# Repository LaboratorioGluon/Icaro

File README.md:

# Ícaro's Sensor Box

Desarrollo de uno de los equipos que van a ser lanzados en el proyecto Ícaro, un proyecto organizado y retransmitido por _@Araba_ST_ y _@Labgluon_ en Twitch.

> [!TIP]
> El proyecto **Ícaro** busca lanzar un globo estratosférico (hasta unos 20-30km de altura), subiendo varios equipos, entre ellos: Uno de radioafionados con APRS y Repetidor U/V, y nuestro equipo de sensores.

Nuestro objetivo es aprender a desarrollar equipos más complejos, a lo que sumamos la dificultad de ser el primer proyecto realizado en comunidad con la gente de _www.twitch.tv/labgluon_. Añadiendo la incertidumbre de gestionar equipos remotos y que no han trabajado nunca juntos..

---
Dentro de las misiones concretas está:
- Prueba de comunicaciones Wifi con ESP32-CAM (o equivalente) y ver máximo rango.
    - Mejorar antenas 2.4Ghz
    - Implementar código de lectura y envío de vídeo por wifi en el ESP32.
- Registro de datos de telemetría de la súbida, y comunicación de estos mediante LoRa.
    - Lectura de BMI160, BME280, 2x PT1000 y GPS.
    - Envío por LoRa e intentar conectarnos a TinyGS
- Creación de PCBs modulares para:
    - La lectura de sensores GPS/IMU/Temp/Barómetro/...
    - Regulación de voltajes.
    - Comunicaciones

**Otras ideas** que se han planteado:
- Añadir un control a la antena para que apunte siempre al globo.
- Añadir panel solar 
- Poner un ESP32 a la intemperie y ver cuando deja de funcionar.

## Enlaces rápidos

- [Diseño General](Docs/Design.md)
- Modulos:
    - [SupplyBoard](Modules/SupplyBoard/Doc/SupplyBoard.md)
    - [SensorBoard](Modules/SensorBoard/Doc/SensorBoard.md)
    - [CamBoard](Modules/CamBoard/Doc/CameraBoard.md)

## Estructura de carpetas

```
Icaro
├── Docs                    # Documentacion general
│   ├── NamingAndCoding.md  # Normas para nombrar ficheros/variables ...
│   └── Design.md           # Diseño a alto nivel
├── IcaroSW/                # Carpeta donde integramos el software final
│   └── ... 
├── Mechanical/             # Diseños 3D y mecánicos
│   └── ... 
└── Modules/                  
│   ├── <Module>             # Una carpeta por tarjeta
│       ├── Doc             # Documentación de la tarjeta
│       ├── PCB             # Diseño de la PCB
│       ├── Software        # Software si el módulo es uno completo
│       └── Library         # Librería SW para manejar la tarjeta.
|   └── ...
```

La idea es que por cada tarjeta que diseñemos tengamos una librería de software pensada para usar los componentes de esa tarjeta. Y que luego, en _IcaroSW_ se haga el software que se considera el principal.

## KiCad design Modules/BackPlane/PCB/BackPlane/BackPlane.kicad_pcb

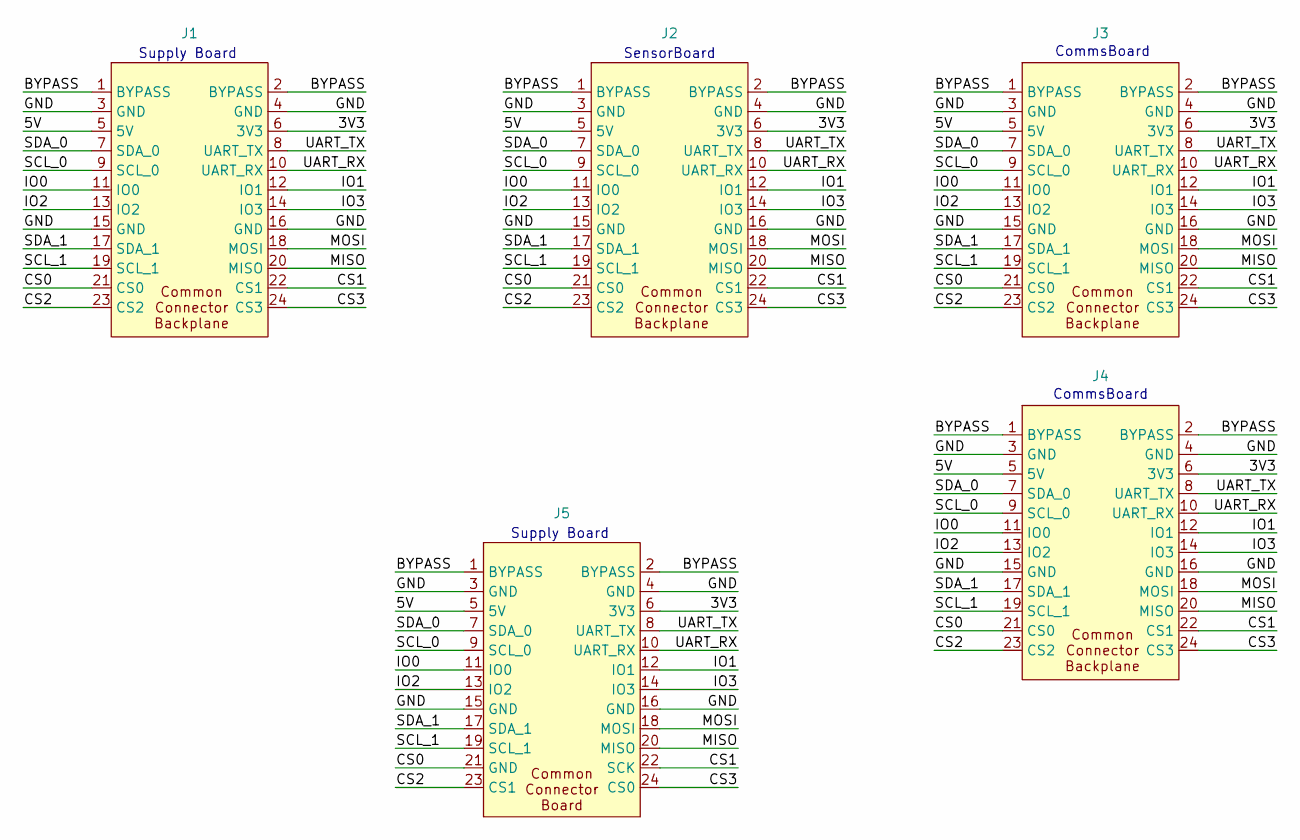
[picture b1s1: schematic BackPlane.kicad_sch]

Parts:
J1, J2, J3, J4: PinSocket_2x12_P2.54mm_Vertical
J5: Connector_Icaro_Edge_tarjeta

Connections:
/3V3: J1.6 (3V3), J2.6 (3V3), J3.6 (3V3), J4.6 (3V3), J5.6 (3V3)
/5V: J1.5 (5V), J2.5 (5V), J3.5 (5V), J4.5 (5V), J5.5 (5V)
/BYPASS: J1.1 (BYPASS), J1.2 (BYPASS), J2.1 (BYPASS), J2.2 (BYPASS), J3.1 (BYPASS), J3.2 (BYPASS), J4.1 (BYPASS), J4.2 (BYPASS), J5.1 (BYPASS), J5.2 (BYPASS)
/CS0: J1.21 (CS0), J2.21 (CS0), J3.21 (CS0), J4.21 (CS0), J5.21 (GND)
/CS1: J1.22 (CS1), J2.22 (CS1), J3.22 (CS1), J4.22 (CS1), J5.22 (SCK)
/CS2: J1.23 (CS2), J2.23 (CS2), J3.23 (CS2), J4.23 (CS2), J5.23 (CS1)
/CS3: J1.24 (CS3), J2.24 (CS3), J3.24 (CS3), J4.24 (CS3), J5.24 (CS0)
/IO0: J1.11 (IO0), J2.11 (IO0), J3.11 (IO0), J4.11 (IO0), J5.11 (IO0)
/IO1: J1.12 (IO1), J2.12 (IO1), J3.12 (IO1), J4.12 (IO1), J5.12 (IO1)
/IO2: J1.13 (IO2), J2.13 (IO2), J3.13 (IO2), J4.13 (IO2), J5.13 (IO2)
/IO3: J1.14 (IO3), J2.14 (IO3), J3.14 (IO3), J4.14 (IO3), J5.14 (IO3)
/MISO: J1.20 (MISO), J2.20 (MISO), J3.20 (MISO), J4.20 (MISO), J5.20 (MISO)
/MOSI: J1.18 (MOSI), J2.18 (MOSI), J3.18 (MOSI), J4.18 (MOSI), J5.18 (MOSI)
/SCL_0: J1.9 (SCL_0), J2.9 (SCL_0), J3.9 (SCL_0), J4.9 (SCL_0), J5.9 (SCL_0)
/SCL_1: J1.19 (SCL_1), J2.19 (SCL_1), J3.19 (SCL_1), J4.19 (SCL_1), J5.19 (SCL_1)
/SDA_0: J1.7 (SDA_0), J2.7 (SDA_0), J3.7 (SDA_0), J4.7 (SDA_0), J5.7 (SDA_0)
/SDA_1: J1.17 (SDA_1), J2.17 (SDA_1), J3.17 (SDA_1), J4.17 (SDA_1), J5.17 (SDA_1)
/UART_RX: J1.10 (UART_RX), J2.10 (UART_RX), J3.10 (UART_RX), J4.10 (UART_RX), J5.10 (UART_RX)
/UART_TX: J1.8 (UART_TX), J2.8 (UART_TX), J3.8 (UART_TX), J4.8 (UART_TX), J5.8 (UART_TX)
GND: J1.3 (GND), J1.4 (GND), J1.15 (GND), J1.16 (GND), J2.3 (GND), J2.4 (GND), J2.15 (GND), J2.16 (GND), J3.3 (GND), J3.4 (GND), J3.15 (GND), J3.16 (GND), J4.3 (GND), J4.4 (GND), J4.15 (GND), J4.16 (GND), J5.3 (GND), J5.4 (GND), J5.15 (GND), J5.16 (GND)

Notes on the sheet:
Supply Board
SensorBoard
CommsBoard

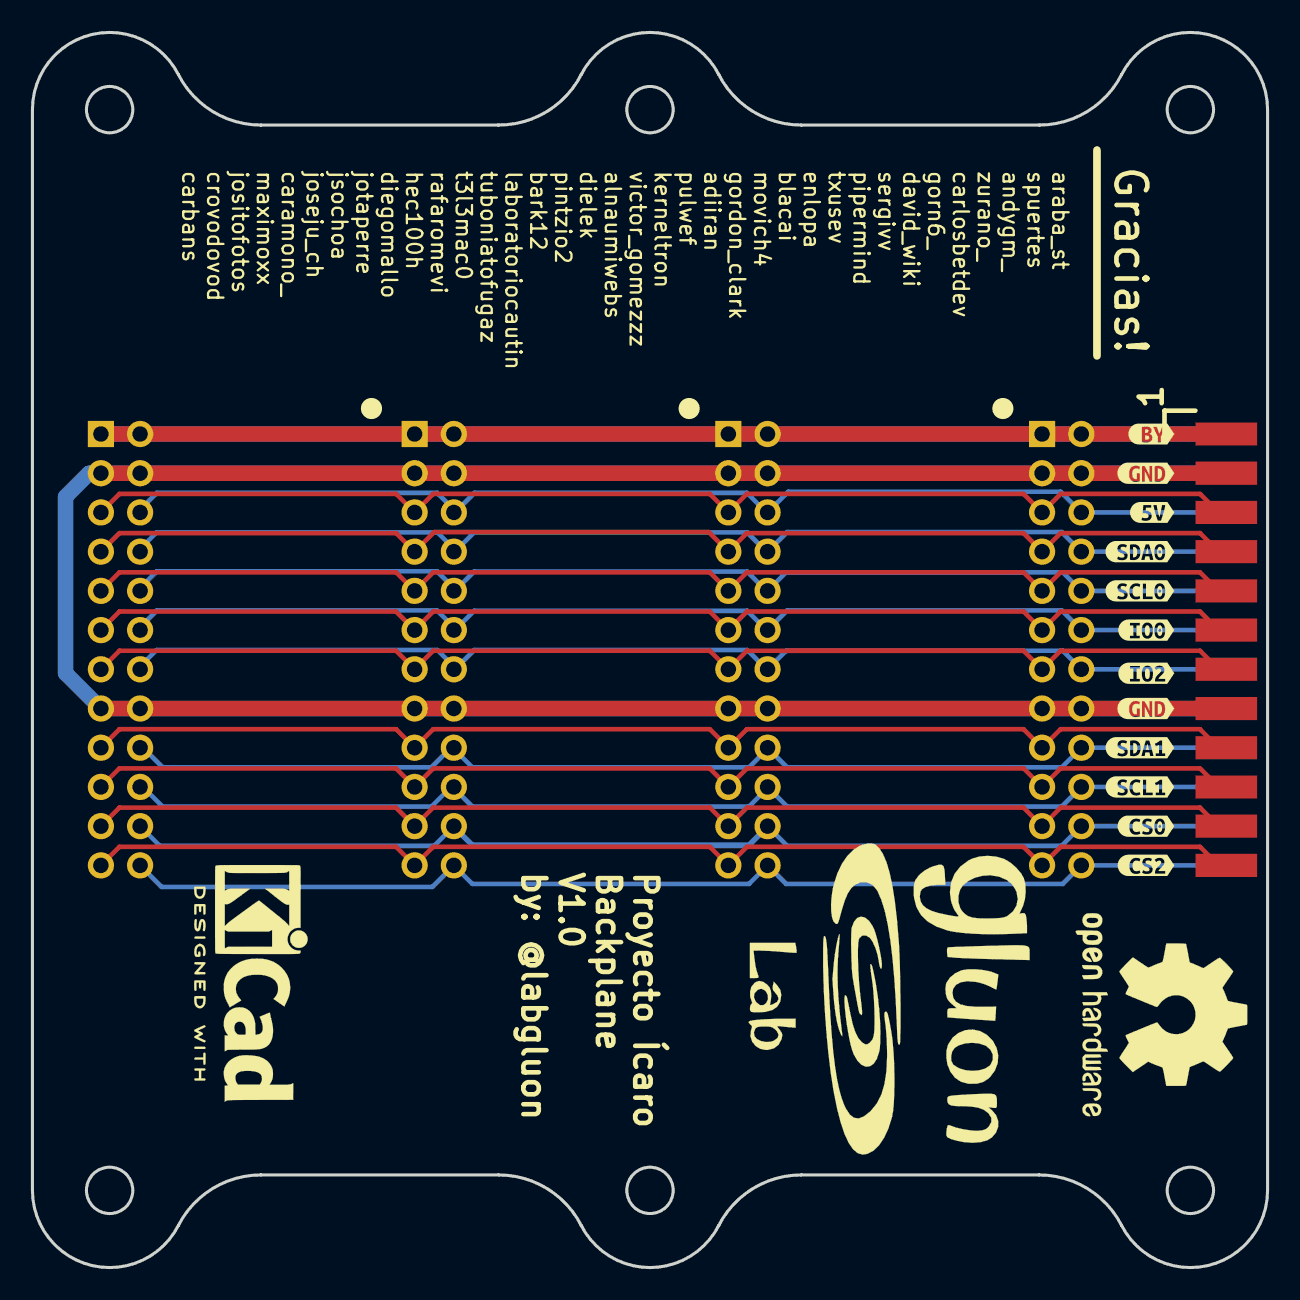
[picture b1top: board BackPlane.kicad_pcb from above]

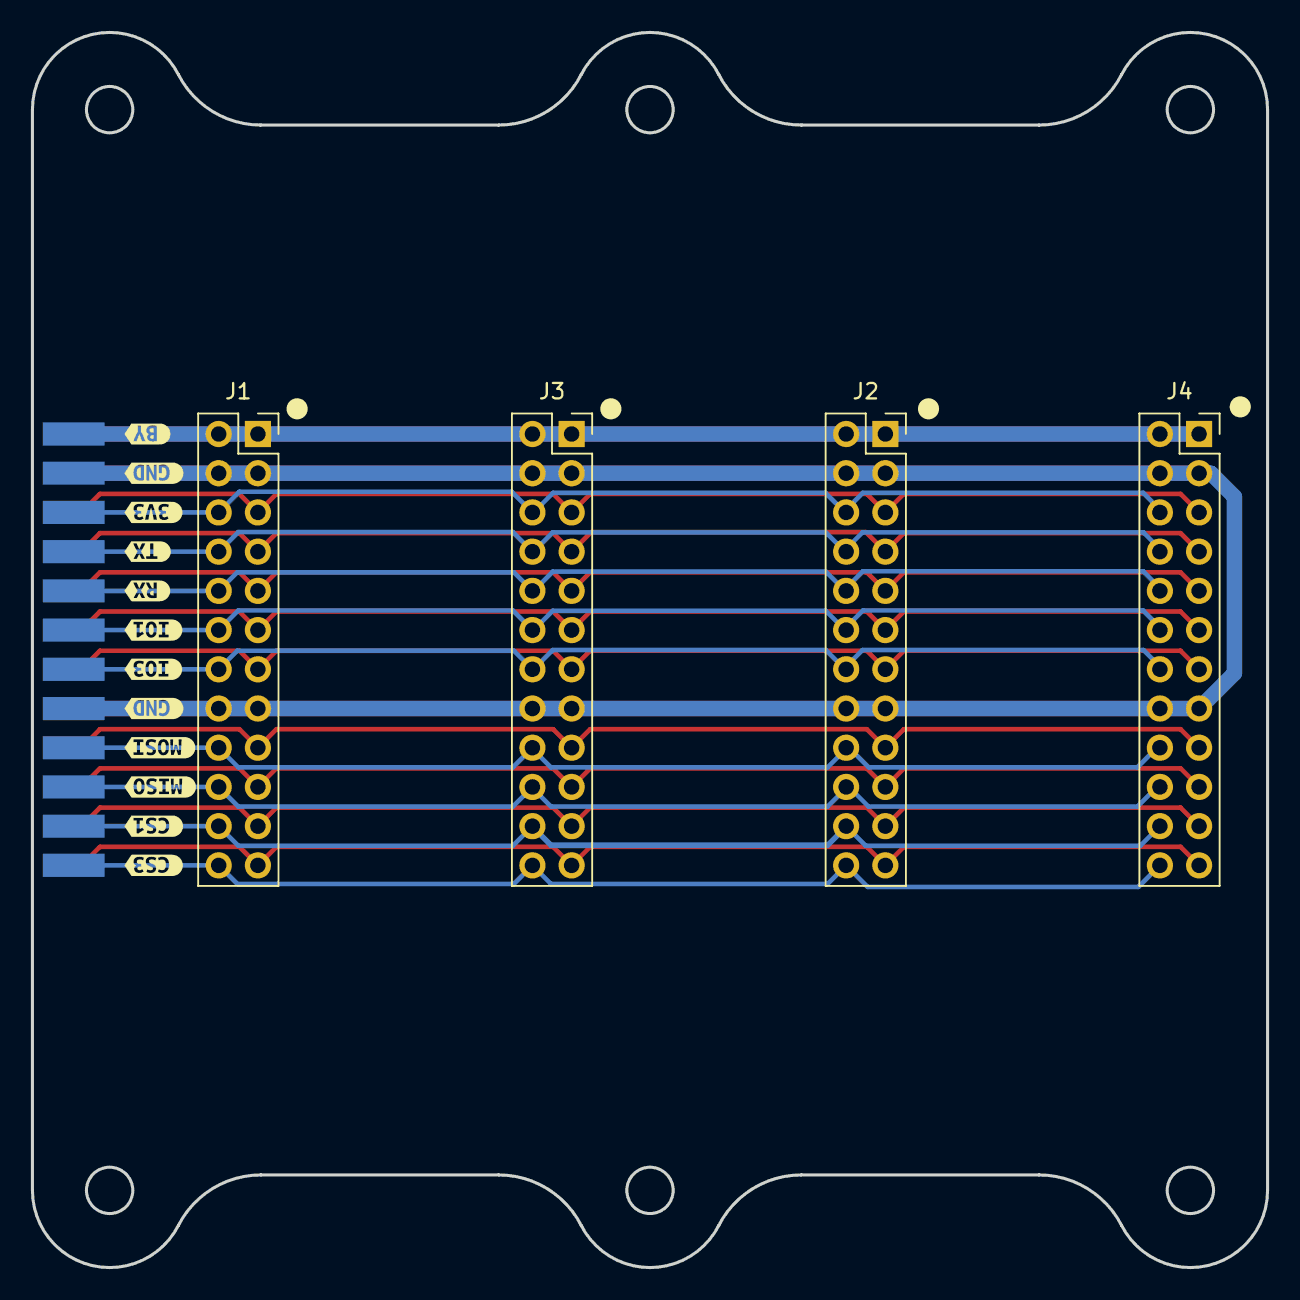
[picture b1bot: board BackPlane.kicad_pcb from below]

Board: 2 copper layers, 80.0 x 80.0 mm, 29 parts (16 on the bottom side), 20 nets.

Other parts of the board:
kibuzzard-67C807F8, kibuzzard-67C807F8#2: G***; kibuzzard-67C807F8
kibuzzard-67C808B4, kibuzzard-67C808B4#2: G***; kibuzzard-67C808B4
kibuzzard-67C808C7: G***; kibuzzard-67C808C7
kibuzzard-67C808DE: G***; kibuzzard-67C808DE
kibuzzard-67C808E6: G***; kibuzzard-67C808E6
kibuzzard-67C808F2: G***; kibuzzard-67C808F2
kibuzzard-67C808FD: G***; kibuzzard-67C808FD
kibuzzard-67C8086E: G***; kibuzzard-67C8086E
kibuzzard-67C8090F: G***; kibuzzard-67C8090F
kibuzzard-67C8091B: G***; kibuzzard-67C8091B
kibuzzard-67C80808, kibuzzard-67C80808#2: G***; kibuzzard-67C80808
kibuzzard-67C80817: G***; kibuzzard-67C80817
kibuzzard-67C80838: G***; kibuzzard-67C80838
kibuzzard-67C80841: G***; kibuzzard-67C80841
kibuzzard-67C80848: G***; kibuzzard-67C80848
kibuzzard-67C80850: G***; kibuzzard-67C80850
kibuzzard-67C80858: G***; kibuzzard-67C80858
kibuzzard-67C80860: G***; kibuzzard-67C80860
kibuzzard-67C80867: G***; kibuzzard-67C80867
kibuzzard-67C80908: G***; kibuzzard-67C80908
kibuzzard-67C80915: G***; kibuzzard-67C80915

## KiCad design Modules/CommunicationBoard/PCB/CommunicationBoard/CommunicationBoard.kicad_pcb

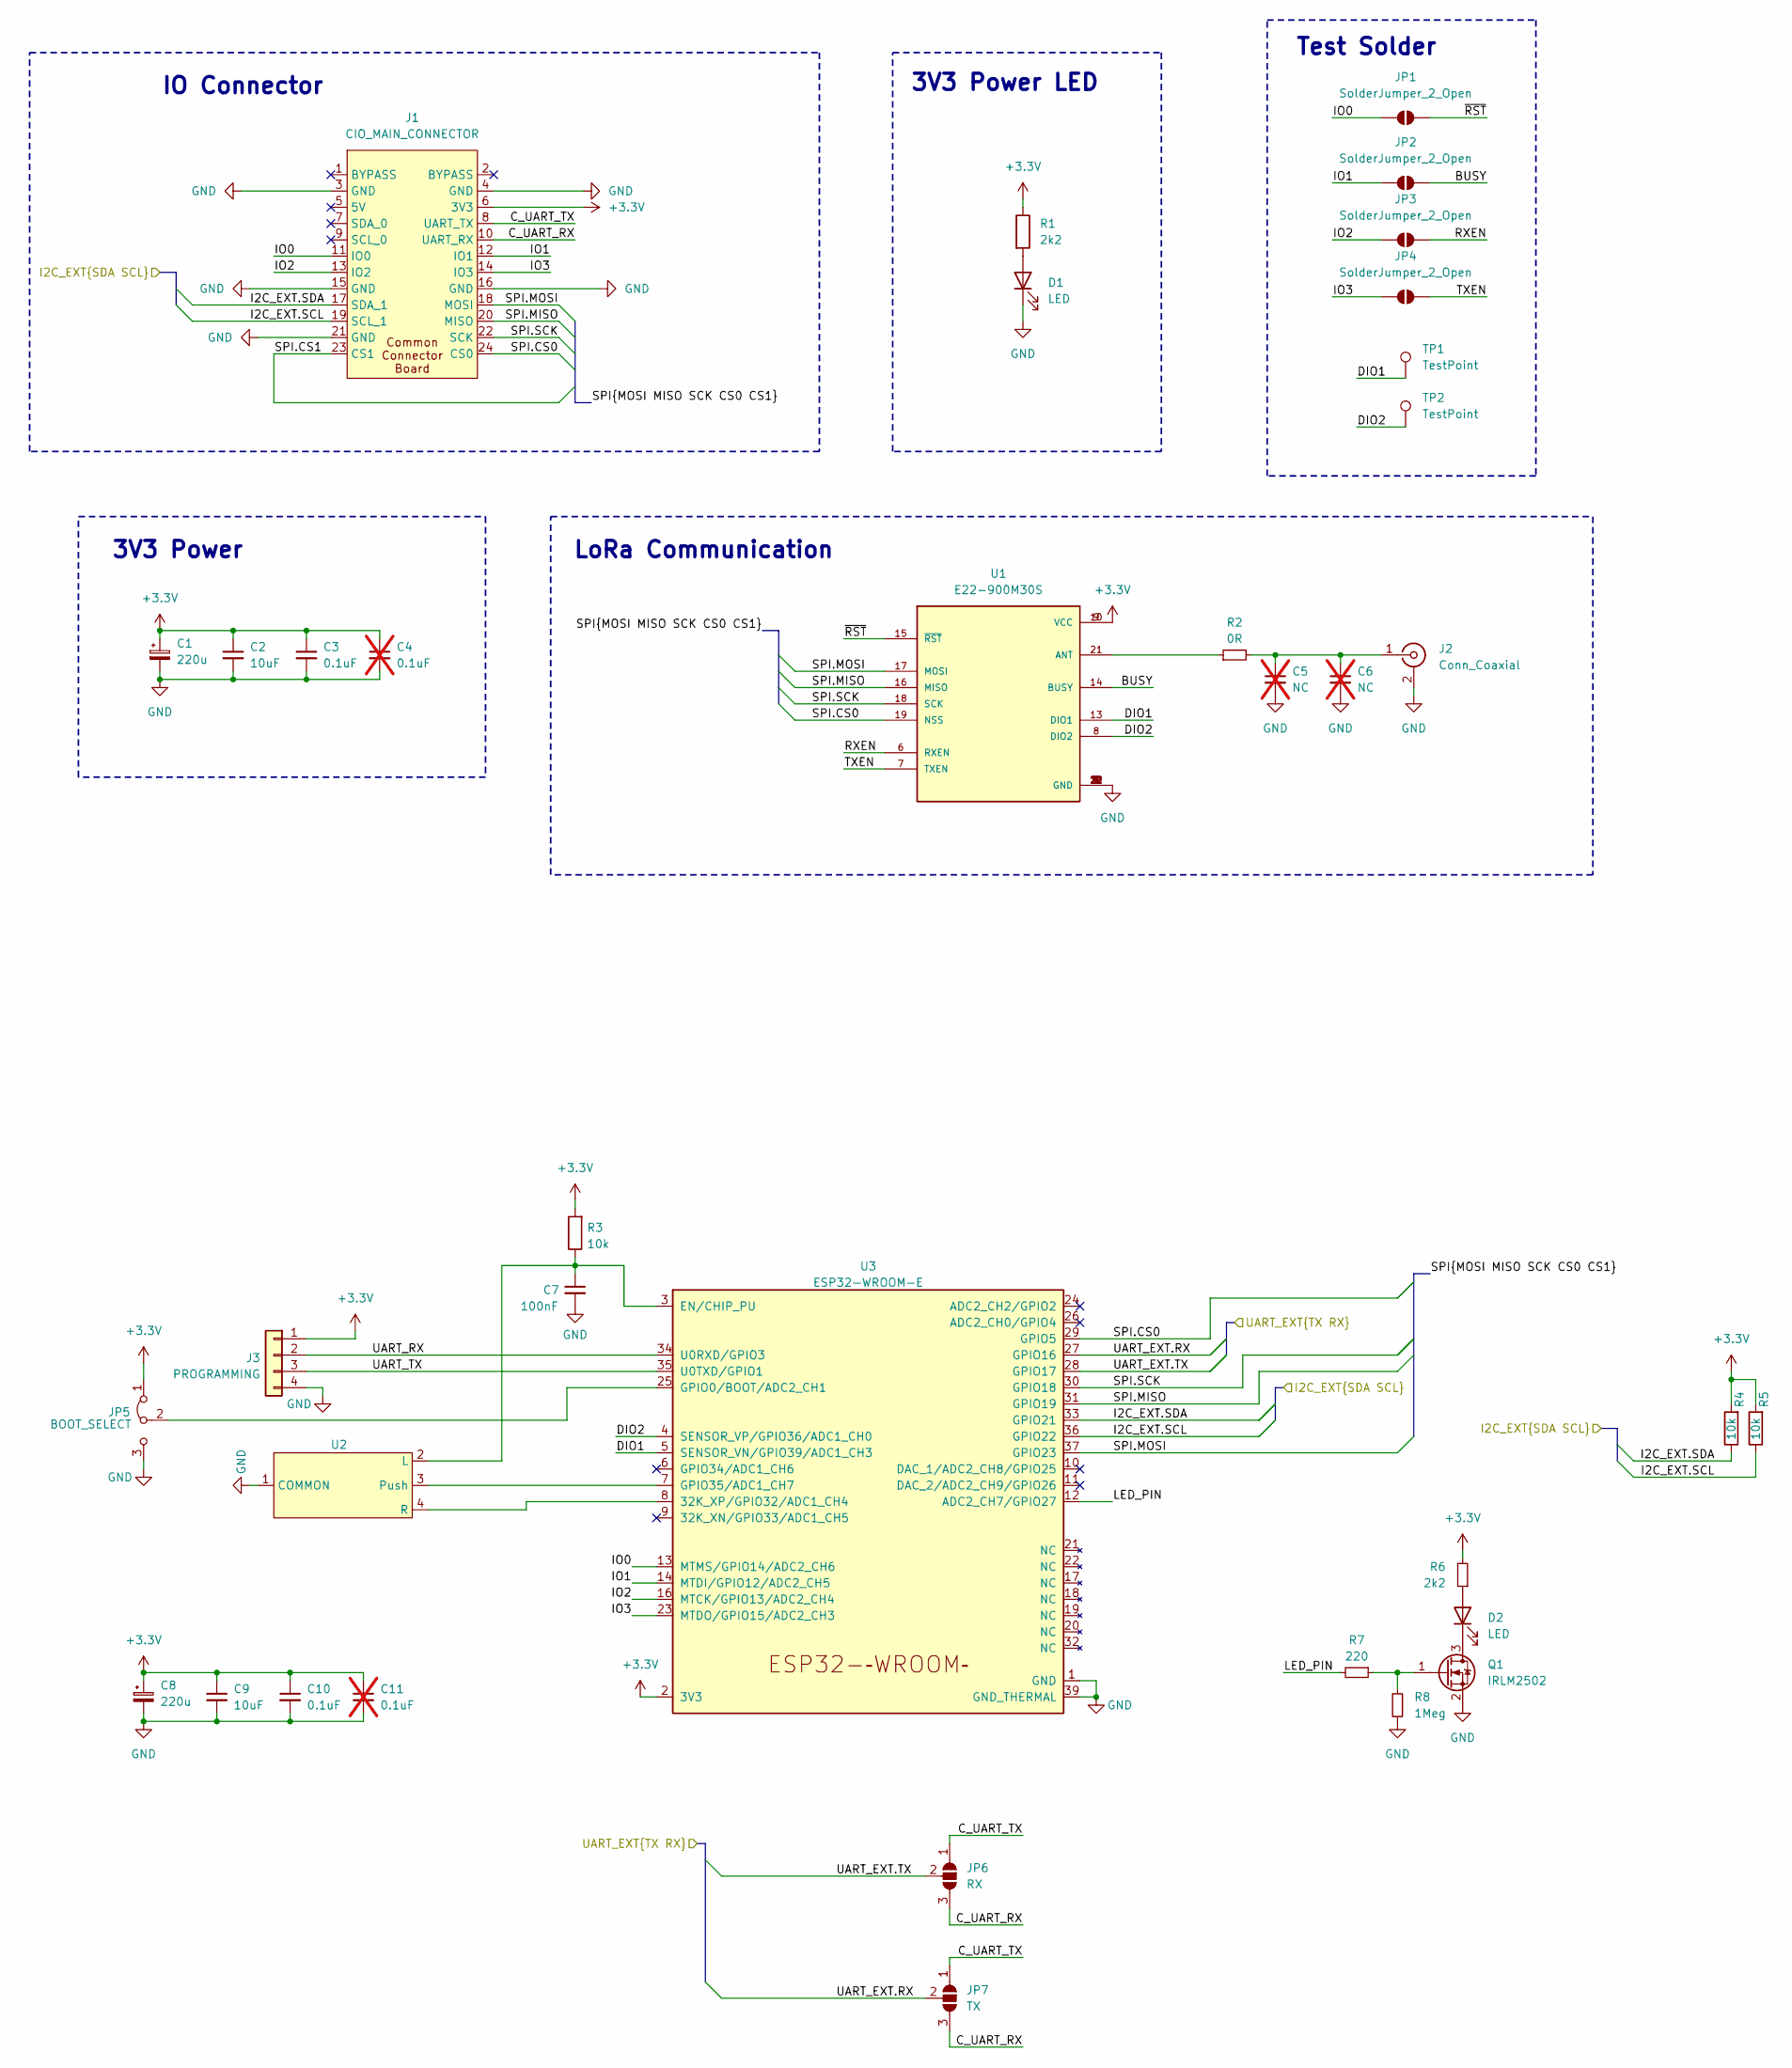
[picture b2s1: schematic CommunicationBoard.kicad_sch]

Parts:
C1, C8: 220u; CP_EIA-3528-21_Kemet-B_Pad1.50x2.35mm_HandSolder
C2, C9: 10uF; C_0603_1608Metric_Pad1.08x0.95mm_HandSolder
C3, C10: 0.1uF; C_0603_1608Metric_Pad1.08x0.95mm_HandSolder
C4, C11: 0.1uF; C_0603_1608Metric_Pad1.08x0.95mm_HandSolder; not fitted
C5, C6: NC; C_0603_1608Metric_Pad1.08x0.95mm_HandSolder; not fitted
C7: 100nF; C_0603_1608Metric_Pad1.08x0.95mm_HandSolder
D1: LED; LED_0603_1608Metric_Pad1.05x0.95mm_HandSolder
D2: LED; LED_0805_2012Metric_Pad1.15x1.40mm_HandSolder
J1: CIO_MAIN_CONNECTOR; Connector_Icaro_Edge_tarjeta
J2: Conn_Coaxial; SMA_132323
J3: PROGRAMMING; PinHeader_1x04_P2.54mm_Vertical
JP1, JP2, JP3, JP4: SolderJumper_2_Open; SolderJumper-2_P1.3mm_Open_RoundedPad1.0x1.5mm
JP5: BOOT_SELECT; PinHeader_1x03_P2.54mm_Vertical
JP6: RX; SolderJumper-3_P1.3mm_Open_Pad1.0x1.5mm
JP7: TX; SolderJumper-3_P1.3mm_Open_Pad1.0x1.5mm
Q1: IRLM2502; SOT-23
R1, R6: 2k2; R_0603_1608Metric_Pad0.98x0.95mm_HandSolder
R2: 0R; R_0603_1608Metric_Pad0.98x0.95mm_HandSolder
R3, R4, R5: 10k; R_0603_1608Metric_Pad0.98x0.95mm_HandSolder
R7: 220; R_0603_1608Metric_Pad0.98x0.95mm_HandSolder
R8: 1Meg; R_0603_1608Metric_Pad0.98x0.95mm_HandSolder
TP1, TP2: TestPoint; TestPoint_Pad_D2.5mm
U1: E22-900M30S; XCVR_E22-900M30S; PARTREV 1.2
U2: WheelSwitch
U3: ESP32-WROOM-E; ESP32-WROOM-32UE

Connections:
+3.3V: C1.1, C2.1, C3.1, C4.1, C8.1, C9.1, C10.1, C11.1, J1.6 (3V3), J3.1, JP5.1 (A), R1.1, R3.2, R4.2, R5.2, R6.2, U1.9 (VCC), U1.10 (VCC), U3.2 (3V3)
/BUSY: JP2.2 (B), U1.14 (BUSY)
/C_UART_RX: J1.10 (UART_RX), JP6.3 (B), JP7.3 (B)
/C_UART_TX: J1.8 (UART_TX), JP6.1 (A), JP7.1 (A)
/DIO1: TP1.1, U1.13 (DIO1), U3.5 (SENSOR_VN/GPIO39/ADC1_CH3)
/DIO2: TP2.1, U1.8 (DIO2), U3.4 (SENSOR_VP/GPIO36/ADC1_CH0)
/I2C_EXT.SCL: J1.19 (SCL_1), R5.1, U3.36 (GPIO22)
/I2C_EXT.SDA: J1.17 (SDA_1), R4.1, U3.33 (GPIO21)
/IO0: J1.11 (IO0), JP1.1 (A), U3.13 (MTMS/GPIO14/ADC2_CH6)
/IO1: J1.12 (IO1), JP2.1 (A), U3.14 (MTDI/GPIO12/ADC2_CH5)
/IO2: J1.13 (IO2), JP3.1 (A), U3.16 (MTCK/GPIO13/ADC2_CH4)
/IO3: J1.14 (IO3), JP4.1 (A), U3.23 (MTDO/GPIO15/ADC2_CH3)
/LED_PIN: R7.2, U3.12 (ADC2_CH7/GPIO27)
/RXEN: JP3.2 (B), U1.6 (RXEN)
/SPI.CS0: J1.24 (CS0), U1.19 (NSS), U3.29 (GPIO5)
/SPI.CS1: J1.23 (CS1)
/SPI.MISO: J1.20 (MISO), U1.16 (MISO), U3.31 (GPIO19)
/SPI.MOSI: J1.18 (MOSI), U1.17 (MOSI), U3.37 (GPIO23)
/SPI.SCK: J1.22 (SCK), U1.18 (SCK), U3.30 (GPIO18)
/TXEN: JP4.2 (B), U1.7 (TXEN)
/UART_EXT.RX: JP7.2 (C), U3.27 (GPIO16)
/UART_EXT.TX: JP6.2 (C), U3.28 (GPIO17)
/UART_RX: J3.2, U3.34 (U0RXD/GPIO3)
/UART_TX: J3.3, U3.35 (U0TXD/GPIO1)
/~RST: JP1.2 (B), U1.15 (~RST)
GND: C1.2, C2.2, C3.2, C4.2, C5.2, C6.2, C7.2, C8.2, C9.2, C10.2, C11.2, D1.1 (K), J1.3 (GND), J1.4 (GND), J1.15 (GND), J1.16 (GND), J1.21 (GND), J2.2 (Ext), J3.4, JP5.3 (B), Q1.2 (S), R8.1, U1.1 (GND), U1.2 (GND), U1.3 (GND), U1.4 (GND), U1.5 (GND), U1.11 (GND), U1.12 (GND), U1.20 (GND), U1.22 (GND), U2.1 (COMMON), U3.1 (GND), U3.15 (GND), U3.38 (GND), U3.39 (GND_THERMAL)
unnamed: D1.2 (A), R1.2
unnamed: D2.2 (A), R6.1
unnamed: D2.1 (K), Q1.3 (D)
unnamed: C5.1, C6.1, J2.1 (In), R2.2
unnamed: JP5.2 (C), U3.25 (GPIO0/BOOT/ADC2_CH1)
unnamed: Q1.1 (G), R7.1, R8.2
unnamed: R2.1, U1.21 (ANT)
unnamed: C7.1, R3.1, U2.2 (L), U3.3 (EN/CHIP_PU)
unnamed: U2.3 (Push), U3.7 (GPIO35/ADC1_CH7)
unnamed: U2.4 (R), U3.8 (32K_XP/GPIO32/ADC1_CH4)

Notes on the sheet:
LoRa Communication
3V3 Power
3V3 Power LED
Test Solder
IO Connector

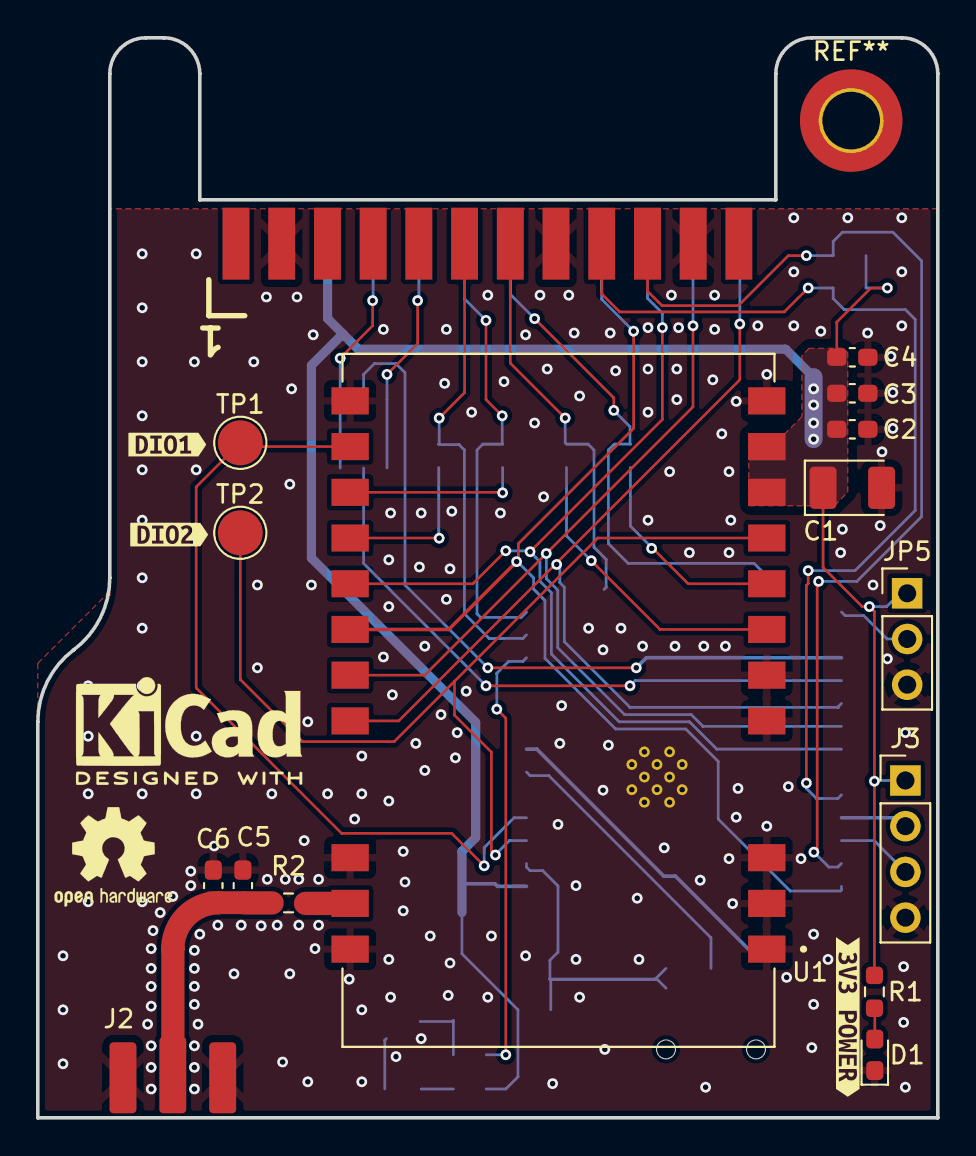
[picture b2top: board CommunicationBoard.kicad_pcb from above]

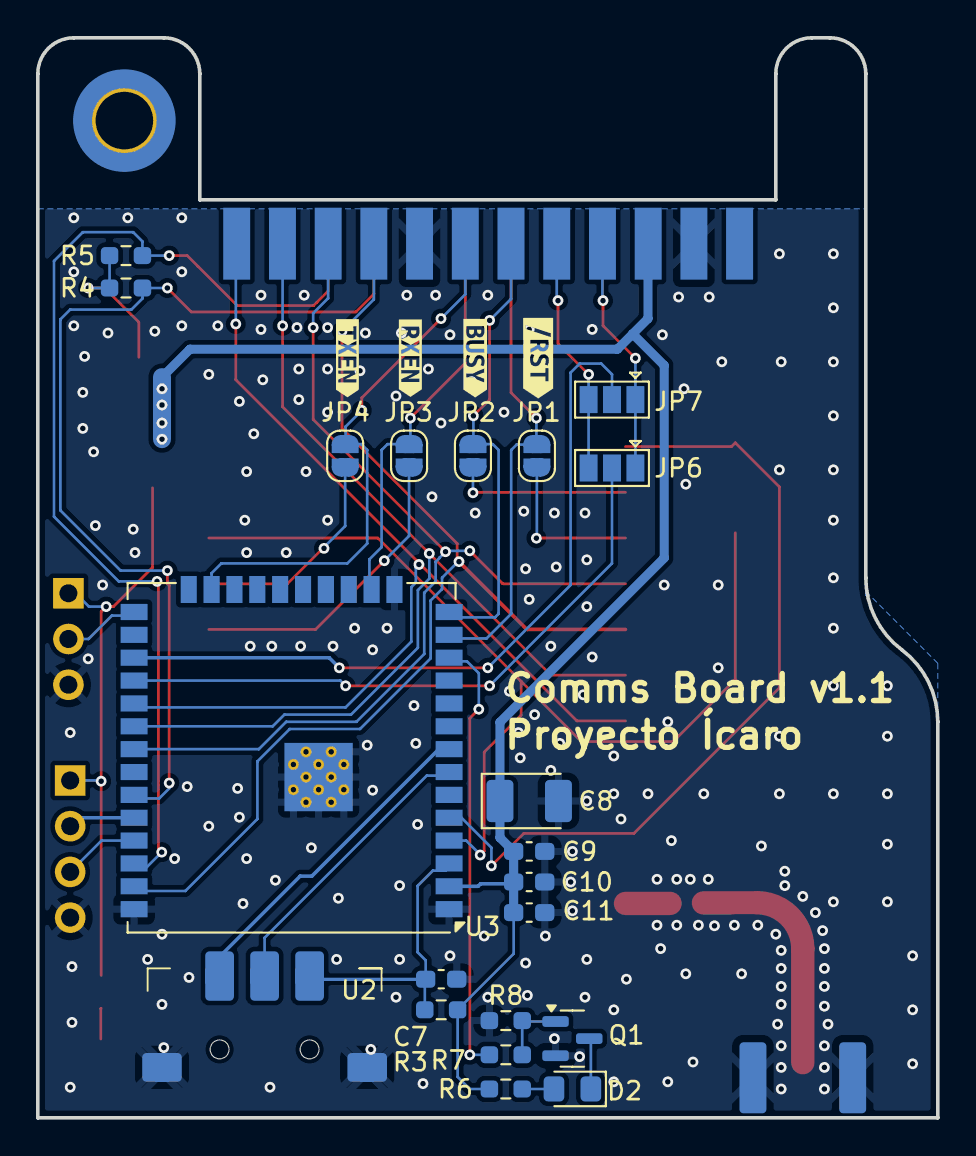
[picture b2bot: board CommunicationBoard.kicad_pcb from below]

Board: 2 copper layers, 50.0 x 60.0 mm, 44 parts (25 on the bottom side), 35 nets.

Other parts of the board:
kibuzzard-67F40C7C: G***; kibuzzard-67F40C7C
kibuzzard-67F40C11: G***; kibuzzard-67F40C11
kibuzzard-67F40C24: G***; kibuzzard-67F40C24
kibuzzard-67F40C92: G***; kibuzzard-67F40C92
kibuzzard-67F40CAD: G***; kibuzzard-67F40CAD
kibuzzard-67F40CB8: G***; kibuzzard-67F40CB8
kibuzzard-67F40CCD: G***; kibuzzard-67F40CCD

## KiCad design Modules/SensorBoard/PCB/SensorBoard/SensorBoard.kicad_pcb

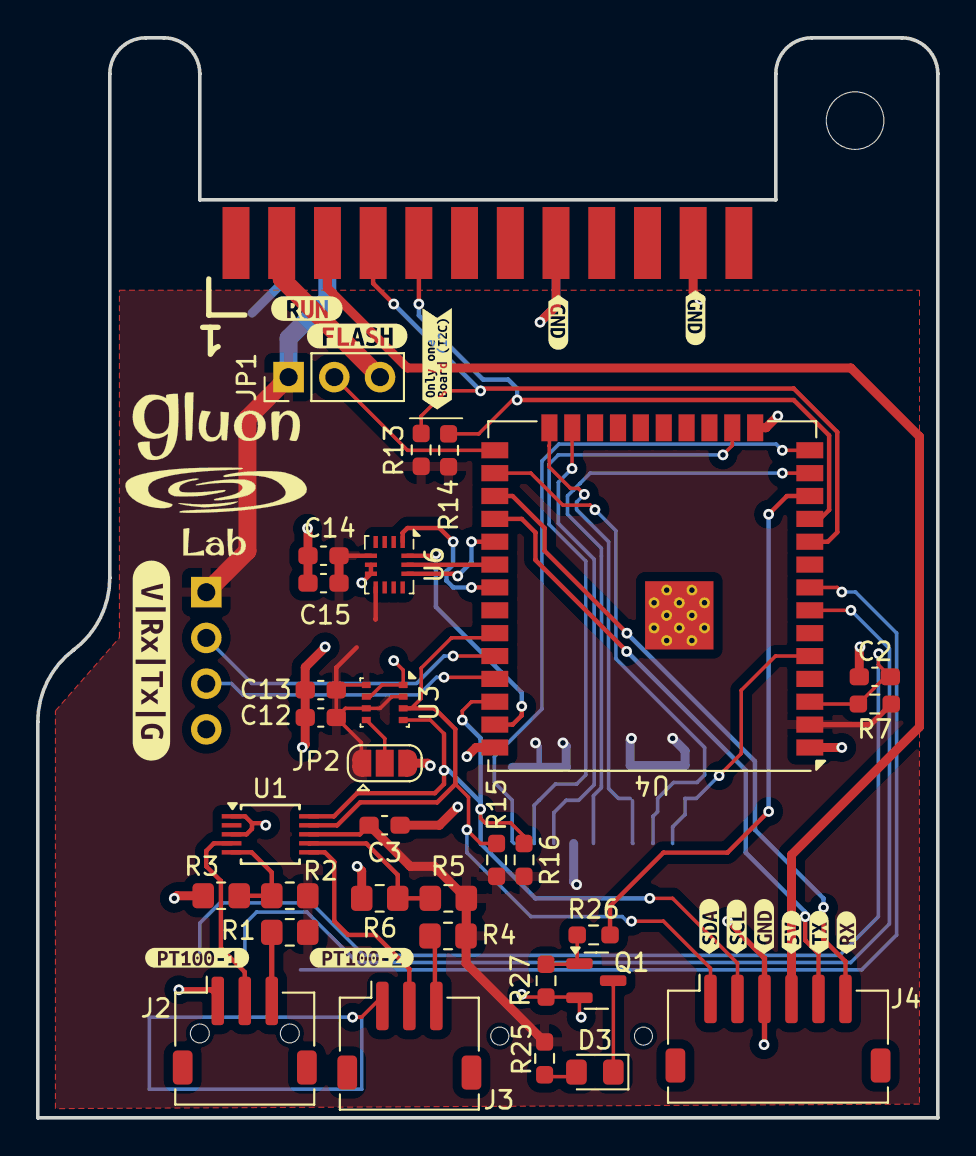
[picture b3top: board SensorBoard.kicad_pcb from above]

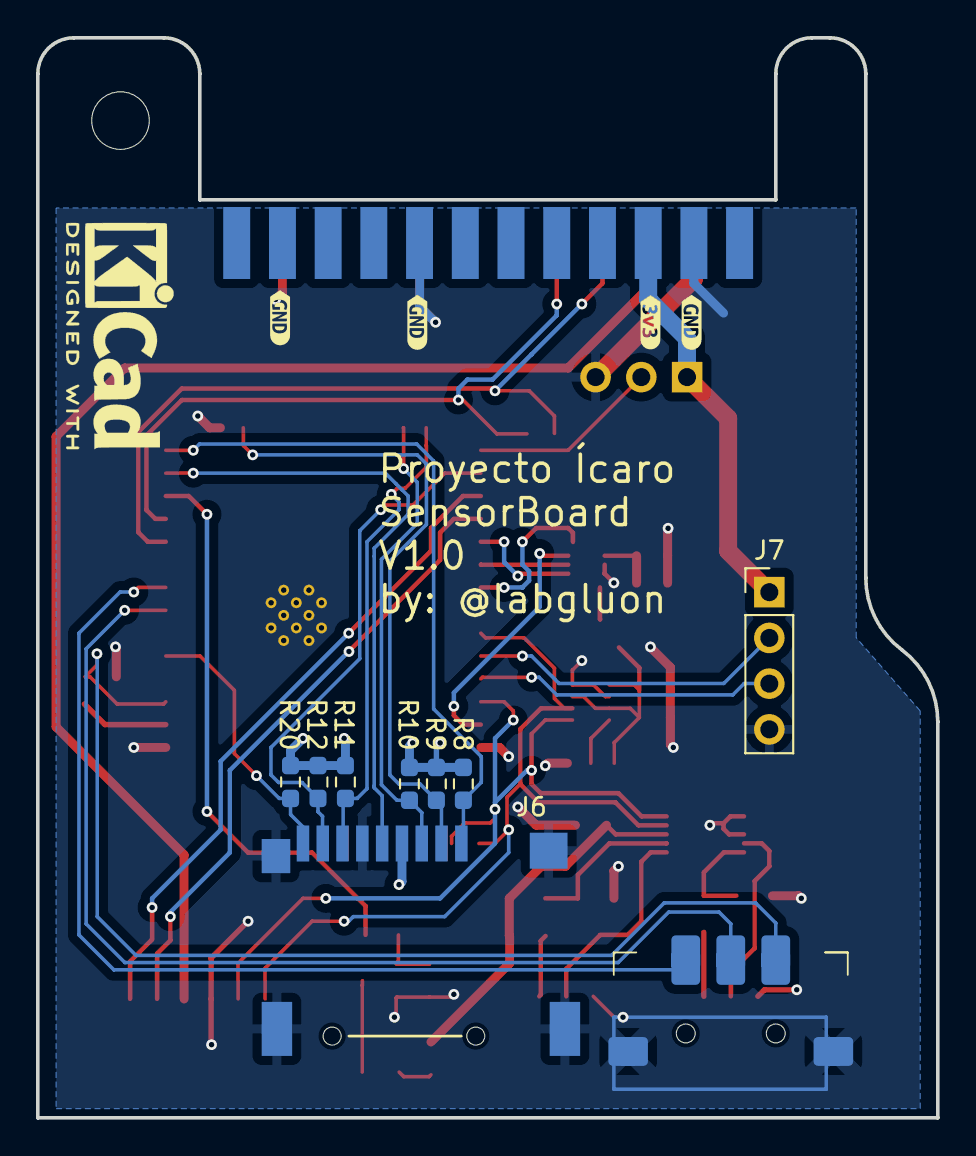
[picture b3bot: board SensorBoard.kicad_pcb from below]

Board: 2 copper layers, 50.0 x 60.0 mm, 59 parts (13 on the bottom side), 37 nets.

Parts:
C2, C3, C12, C13, C14, C15: 100nF; C_0603_1608Metric_Pad1.08x0.95mm_HandSolder
D3: LED; LED_0805_2012Metric_Pad1.15x1.40mm_HandSolder
J1: Connector_Icaro_Edge_tarjeta
J2: PT100_1; JST_ZH_S3B-ZR-SM4A-TF_1x03-1MP_P1.50mm_Horizontal
J3: PT100_2; JST_ZH_S3B-ZR-SM4A-TF_1x03-1MP_P1.50mm_Horizontal
J4: Conn_01x06; JST_ZH_S6B-ZR-SM4A-TF_1x06-1MP_P1.50mm_Horizontal
J6: Micro_SD_Card; microSD-Receptacle-SelfEject
J7: PROGRAMMING; PinHeader_1x04_P2.54mm_Vertical
JP1: BOOT_SELECT; PinHeader_1x03_P2.54mm_Vertical
JP2: BME280_Addr_Sel; SolderJumper-3_P1.3mm_Open_RoundedPad1.0x1.5mm
Q1: IRLM2502; SOT-23
R1, R2, R4, R5: 1k; R_0805_2012Metric_Pad1.20x1.40mm_HandSolder
R3, R6: 68; R_0805_2012Metric_Pad1.20x1.40mm_HandSolder
R7, R8, R9, R10, R11, R12, R13, R14, R15, R16, R20: 10k; R_0603_1608Metric_Pad0.98x0.95mm_HandSolder
R25: 2k2; R_0603_1608Metric_Pad0.98x0.95mm_HandSolder
R26: 220; R_0603_1608Metric_Pad0.98x0.95mm_HandSolder
R27: 1Meg; R_0603_1608Metric_Pad0.98x0.95mm_HandSolder
U1: ADS1115IDGS; TSSOP-10_3x3mm_P0.5mm
U2: WheelSwitch
U3: BME280; Bosch_LGA-8_2.5x2.5mm_P0.65mm_ClockwisePinNumbering
U4: ESP32-WROOM-E; ESP32-WROOM-32UE
U6: BMI160; Bosch_LGA-14_3x2.5mm_P0.5mm
kibuzzard-67C3A9D6: G***; kibuzzard-67C3A9D6
kibuzzard-67C3A99D: G***; kibuzzard-67C3A99D
kibuzzard-67C3AA69: G***; kibuzzard-67C3AA69
kibuzzard-67C3AA71: G***; kibuzzard-67C3AA71
kibuzzard-67C3AA85: G***; kibuzzard-67C3AA85
kibuzzard-67C3AAB2, kibuzzard-67C3AAB2#2, kibuzzard-67C3AAB2#3, kibuzzard-67C3AAB2#4, kibuzzard-67C3AAB2#5, kibuzzard-67C3AAB2#6: G***; kibuzzard-67C3AAB2
kibuzzard-67C3AABB: G***; kibuzzard-67C3AABB
kibuzzard-67C3AAC1: G***; kibuzzard-67C3AAC1
kibuzzard-67C3AAC6: G***; kibuzzard-67C3AAC6
kibuzzard-67C3AB9B: G***; kibuzzard-67C3AB9B
kibuzzard-67C3AC34: G***; kibuzzard-67C3AC34
kibuzzard-67C4846B: G***; kibuzzard-67C4846B
kibuzzard-67C81440: G***; kibuzzard-67C81440

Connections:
+3V3: C3.1, C12.1, C13.1, C14.1, C15.1, J1.6 (3V3), J6.4 (VDD), J7.1, JP1.1 (A), JP2.1 (A), R1.1, R2.1, R4.1, R5.1, R7.2, R8.2, R9.2, R10.2, R11.2, R12.2, R13.2, R14.2, R15.2, R16.2, R20.2, R25.2, U1.8 (VDD), U3.2 (CSB), U3.6 (VDDIO), U3.8 (VDD), U4.2 (3V3), U6.5 (VDDIO), U6.8 (VDD)
+5V: J1.5 (5V), J4.4
/Microcontroller/CD_DETECT: J6.9 (CD), R20.1, U4.5 (SENSOR_VN/GPIO39/ADC1_CH3)
/Microcontroller/I2C_EXT.SCL: J1.9 (SCL_0), R14.1, U4.11 (DAC_2/ADC2_CH9/GPIO26)
/Microcontroller/I2C_EXT.SDA: J1.7 (SDA_0), R13.1, U4.10 (DAC_1/ADC2_CH8/GPIO25)
/Microcontroller/I2C_INT.SCL: J4.2, R16.1, U1.10 (SCL), U3.4 (SCK), U4.36 (GPIO22)
/Microcontroller/I2C_INT.SDA: J4.1, R15.1, U1.9 (SDA), U3.3 (SDI), U4.33 (GPIO21)
/Microcontroller/LED_PIN: R26.2, U4.12 (ADC2_CH7/GPIO27)
/Microcontroller/SD_CLK: J6.5 (CLK), U4.13 (MTMS/GPIO14/ADC2_CH6)
/Microcontroller/SD_CMD: J6.3 (CMD), R10.1, U4.23 (MTDO/GPIO15/ADC2_CH3)
/Microcontroller/SD_DATA0: J6.7 (DAT0), R11.1, U4.24 (ADC2_CH2/GPIO2)
/Microcontroller/SD_DATA1: J6.8 (DAT1), R12.1, U4.26 (ADC2_CH0/GPIO4)
/Microcontroller/SD_DATA2: J6.1 (DAT2), R8.1, U4.14 (MTDI/GPIO12/ADC2_CH5)
/Microcontroller/SD_DATA3: J6.2 (DAT3/CD), R9.1, U4.16 (MTCK/GPIO13/ADC2_CH4)
/Microcontroller/SPI_IMU.CS0: U4.29 (GPIO5), U6.12 (CSB)
/Microcontroller/SPI_IMU.MISO: U4.31 (GPIO19), U6.1 (SDO)
/Microcontroller/SPI_IMU.MOSI: U4.37 (GPIO23), U6.14 (SDx)
/Microcontroller/SPI_IMU.SCK: U4.30 (GPIO18), U6.13 (SCx)
/Microcontroller/UART_GPS.RX: J4.6, U4.27 (GPIO16)
/Microcontroller/UART_GPS.TX: J4.5, U4.28 (GPIO17)
/Microcontroller/UART_RX: J7.2, U4.34 (U0RXD/GPIO3)
/Microcontroller/UART_TX: J7.3, U4.35 (U0TXD/GPIO1)
/PT100/PT100_1_N: R2.2, R3.1, U1.5 (AIN1)
/PT100/PT100_1_P: J2.2, U1.4 (AIN0)
/PT100/PT100_2_N: R5.2, R6.1, U1.7 (AIN3)
/PT100/PT100_2_P: J3.2, U1.6 (AIN2)
GND: C2.2, C3.2, C12.2, C13.2, C14.2, C15.2, J1.3 (GND), J1.4 (GND), J1.15 (GND), J1.16 (GND), J1.21 (GND), J2.1, J3.1, J4.3, J6.6 (VSS), J6.11 (SHIELD), J7.4, JP1.3 (B), JP2.3 (B), Q1.2 (S), R3.2, R6.2, R27.1, U1.1 (ADDR), U1.3 (GND), U2.1 (COMMON), U3.1 (GND), U3.7 (GND), U4.1 (GND), U4.15 (GND), U4.38 (GND), U4.39 (GND_THERMAL), U6.6 (GNDIO), U6.7 (GND)
unnamed: D3.2 (A), R25.1
unnamed: D3.1 (K), Q1.3 (D)
unnamed: J2.3, R1.2
unnamed: J3.3, R4.2
unnamed: JP1.2 (C), U4.25 (GPIO0/BOOT/ADC2_CH1)
unnamed: JP2.2 (C), U3.5 (SDO)
unnamed: Q1.1 (G), R26.1, R27.2
unnamed: C2.1, R7.1, U2.2 (L), U4.3 (EN/CHIP_PU)
unnamed: U2.3 (Push), U4.7 (GPIO35/ADC1_CH7)
unnamed: U2.4 (R), U4.8 (32K_XP/GPIO32/ADC1_CH4)
